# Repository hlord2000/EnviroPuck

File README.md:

# EnviroPuck 🌍
Introducing the EnviroPuck, a sleek and low-power environment sensing device, utilizing Raytac's MDBT50Q module featuring the nRF52840 chip, and Bosch's BME688 environmental sensor.

# Features 🎛️
- Raytac MDBT50Q Module with nRF52840: Enables robust wireless connectivity, supporting Matter/Thread protocols 📡
- BME688 Sensor: Accurately monitors temperature, humidity, pressure, and gas conditions 🌡️💧🌀
- Low Power Design: Powered by a single primary cell CR2032, engineered for energy efficiency and long-lasting performance 🔋

# Applications 🏠
- The EnviroPuck is ideal for home automation, indoor climate monitoring, and various IoT applications requiring environmental data.

# Development Status ⚙️
- Hardware: Prototyped
- Firmware: TODO 
- Mechanical Design: TODO

# License 📄
- This project is released under the CERN Open Hardware License V2 - Permissive. More details can be found in the LICENSE file included in the project.

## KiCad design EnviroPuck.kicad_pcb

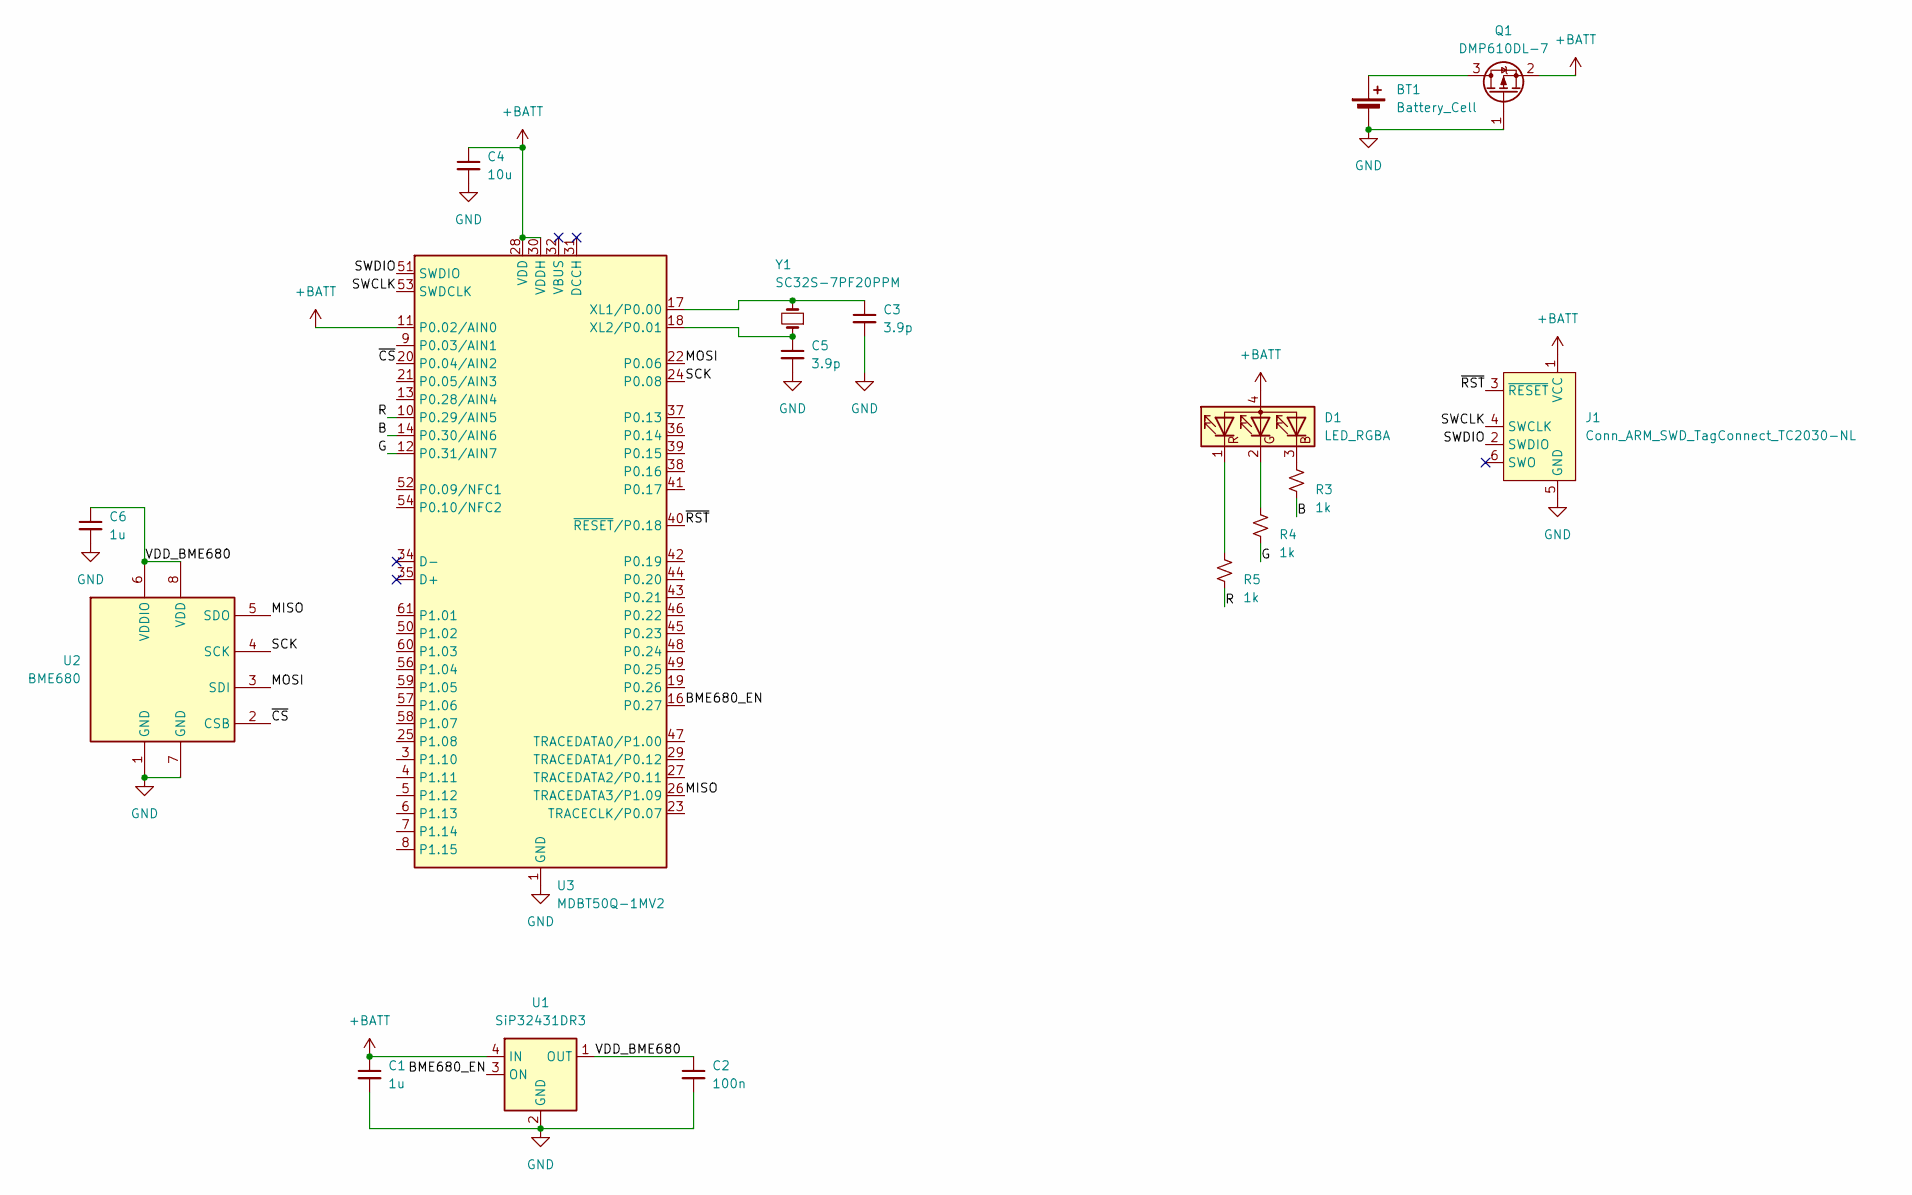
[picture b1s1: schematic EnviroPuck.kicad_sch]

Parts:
BT1: Battery_Cell; BatteryHolder_Multicomp_BC-2001_1x2032
C1, C6: 1u; C_0402_1005Metric; MPN GRM153C80G105ME15D
C2: 100n; C_0402_1005Metric; MPN CL05B104KA5NNNC
C3, C5: 3.9p; C_0201_0603Metric; MPN GRT0335C1H3R9CA02D
C4: 10u; C_0805_2012Metric; MPN CL21A106KOQNNNE
D1: LED_RGBA; LED_Lumex_SML-LX0404SIUPGUSB
J1: Conn_ARM_SWD_TagConnect_TC2030-NL; Tag-Connect_TC2030-IDC-NL_2x03_P1.27mm_Vertical
Q1: DMP610DL-7; SOT-23; MPN DMP610DL-7
R3, R4, R5: 1k; R_0805_2012Metric; MPN ERJ-6GEYJ102V
U1: SiP32431DR3; SOT-363_SC-70-6
U2: BME680; Bosch_LGA-8_3x3mm_P0.8mm_ClockwisePinNumbering
U3: MDBT50Q-1MV2; Raytac_MDBT50Q
Y1: SC32S-7PF20PPM; Crystal_SMD_3215-2Pin_3.2x1.5mm; MPN SC32S-7PF20PPM

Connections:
+BATT: C1.1, C4.1, D1.4 (A), J1.1 (VCC), Q1.2 (S), U1.4 (IN), U3.11 (P0.02/AIN0), U3.28 (VDD), U3.30 (VDDH)
/B: R3.2, U3.14 (P0.30/AIN6)
/BME680_EN: U1.3 (ON), U3.16 (P0.27)
/G: R4.2, U3.12 (P0.31/AIN7)
/MISO: U2.5 (SDO), U3.26 (TRACEDATA3/P1.09)
/MOSI: U2.3 (SDI), U3.22 (P0.06)
/R: R5.2, U3.10 (P0.29/AIN5)
/SCK: U2.4 (SCK), U3.24 (P0.08)
/SWCLK: J1.4 (SWCLK), U3.53 (SWDCLK)
/SWDIO: J1.2 (SWDIO), U3.51 (SWDIO)
/VDD_BME680: C2.1, C6.1, U1.1 (OUT), U2.6 (VDDIO), U2.8 (VDD)
/~CS: U2.2 (CSB), U3.20 (P0.04/AIN2)
/~RST: J1.3 (~RESET), U3.40 (~RESET/P0.18)
GND: BT1.2 (-), C1.2, C2.2, C3.2, C4.2, C5.2, C6.2, J1.5 (GND), Q1.1 (G), U1.2 (GND), U1.5 (GND), U2.1 (GND), U2.7 (GND), U3.1 (GND), U3.2 (GND), U3.15 (GND), U3.33 (GND), U3.55 (GND)
unnamed: BT1.1 (+), Q1.3 (D)
unnamed: D1.3 (BK), R3.1
unnamed: D1.2 (GK), R4.1
unnamed: D1.1 (RK), R5.1
unnamed: C3.1, U3.17 (XL1/P0.00), Y1.2
unnamed: C5.1, U3.18 (XL2/P0.01), Y1.1

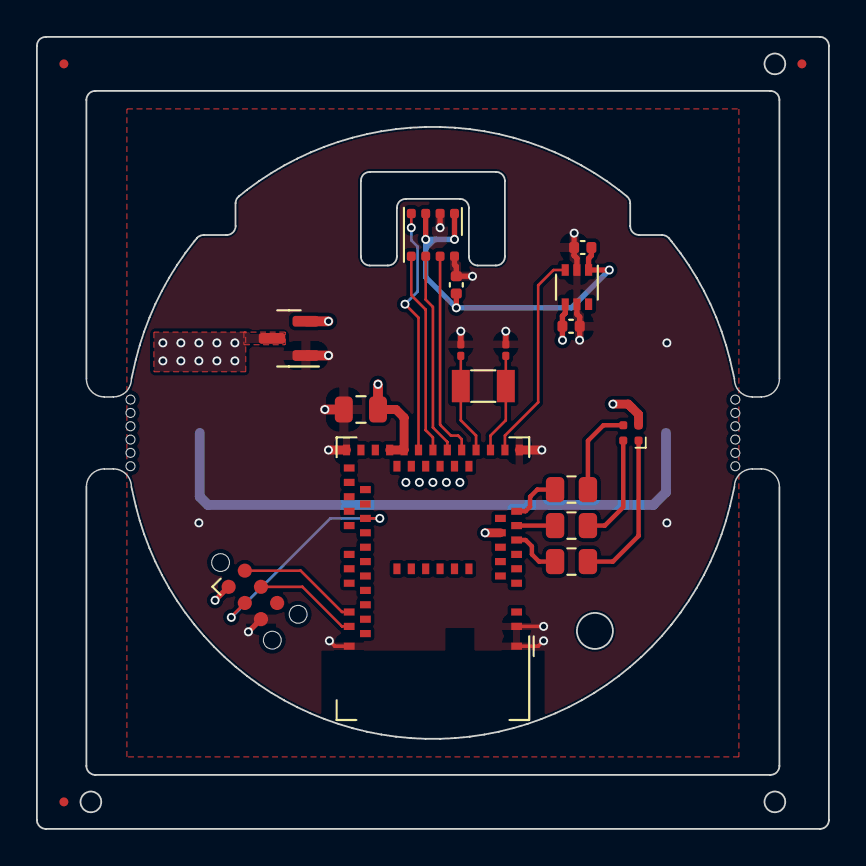
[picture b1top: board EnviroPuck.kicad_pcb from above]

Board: 4 copper layers, 44.0 x 44.0 mm, 17 parts (1 on the bottom side), 20 nets.

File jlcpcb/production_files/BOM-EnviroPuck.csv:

Comment,Designator,Footprint,LCSC
SC32S-7PF20PPM,Y1,Crystal_SMD_3215-2Pin_3.2x1.5mm,
1k,R5,R_0805_2012Metric,
1k,R4,R_0805_2012Metric,
1k,R3,R_0805_2012Metric,
DMP610DL-7,Q1,SOT-23,
1u,C6,C_0402_1005Metric,
3.9p,C5,C_0201_0603Metric,
10u,C4,C_0805_2012Metric,
3.9p,C3,C_0201_0603Metric,
100n,C2,C_0402_1005Metric,
1u,C1,C_0402_1005Metric,
LED_RGBA,D1,LED_Lumex_SML-LX0404SIUPGUSB,
MDBT50Q-1MV2,U3,Raytac_MDBT50Q,
SiP32431DR3,U1,SOT-363_SC-70-6,
BME680,U2,Bosch_LGA-8_3x3mm_P0.8mm_ClockwisePinNumbering,
Battery_Cell,BT1,BatteryHolder_Multicomp_BC-2001_1x2032,

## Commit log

2023-08-09 Initial commit.
